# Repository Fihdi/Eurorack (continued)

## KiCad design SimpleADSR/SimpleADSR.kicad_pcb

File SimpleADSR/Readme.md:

# ADSR module with voltage controllable Sustain level and Release time.

I wasn't using the CV-Features of my VCADSR module at all so I cut out all of the unnecessary CV-parts. At the end I was still left with a pretty big schematic, so I started to reduce it. The finished module now has the following features:

Attack:		Sets the Attack time.

Decay:		Sets the Decay time.

Sustain:	Sets the Sustain level. This can be controlled externally with a control voltage on the SUS input.

Release:	Sets the Release time. This can be controlled externall with a control voltage on the CV input.

GATE:		Gate input, main input to use the module, goes into the decay and sustain phases while this input is high.

TRG:		Trigger input, the module starts the Attack phase regardless in which phase the module currently is.

EOC:		End-of-cycle output, this output becomes high at the end of the release phase.

OUT:		ADSR output.

LOOP:		Loop switch, re-triggers the module at the end of the release phase. Same effect as connecting EOC to GATE or TRG.

Hacks:

Slew Rate Limiter: While the module is in the sustain phase, an external signal can be applied to the SUS input. A slewed version of this signal is output at the OUT jack. The "DECAY" knob controls the slew rate.

The module that you see in the picture above is using circuit boards that were fabricated by [PCBWay](https://www.pcbway.com/). They have excellent build quality and I can recommend using their service to build your own projects! I used the "Black" option for the soldermask and the surface has very deep and glossy black finish, which looks amazing, they also have an option for a "Matte Black" finish which I will try next time. Thank you PCBWay for sponsoring this module. They have very fast response times, not even 20 minutes after uploading the Gerber files I received an E-Mail notifying me about an error in my design (turns out I didn't complete the outline of a board). Afterwards I could re-upload the files and it all worked out. Their chatroom is also readily available, all my questions regarding pricing, delivery and technical details were answered right away in the chat!

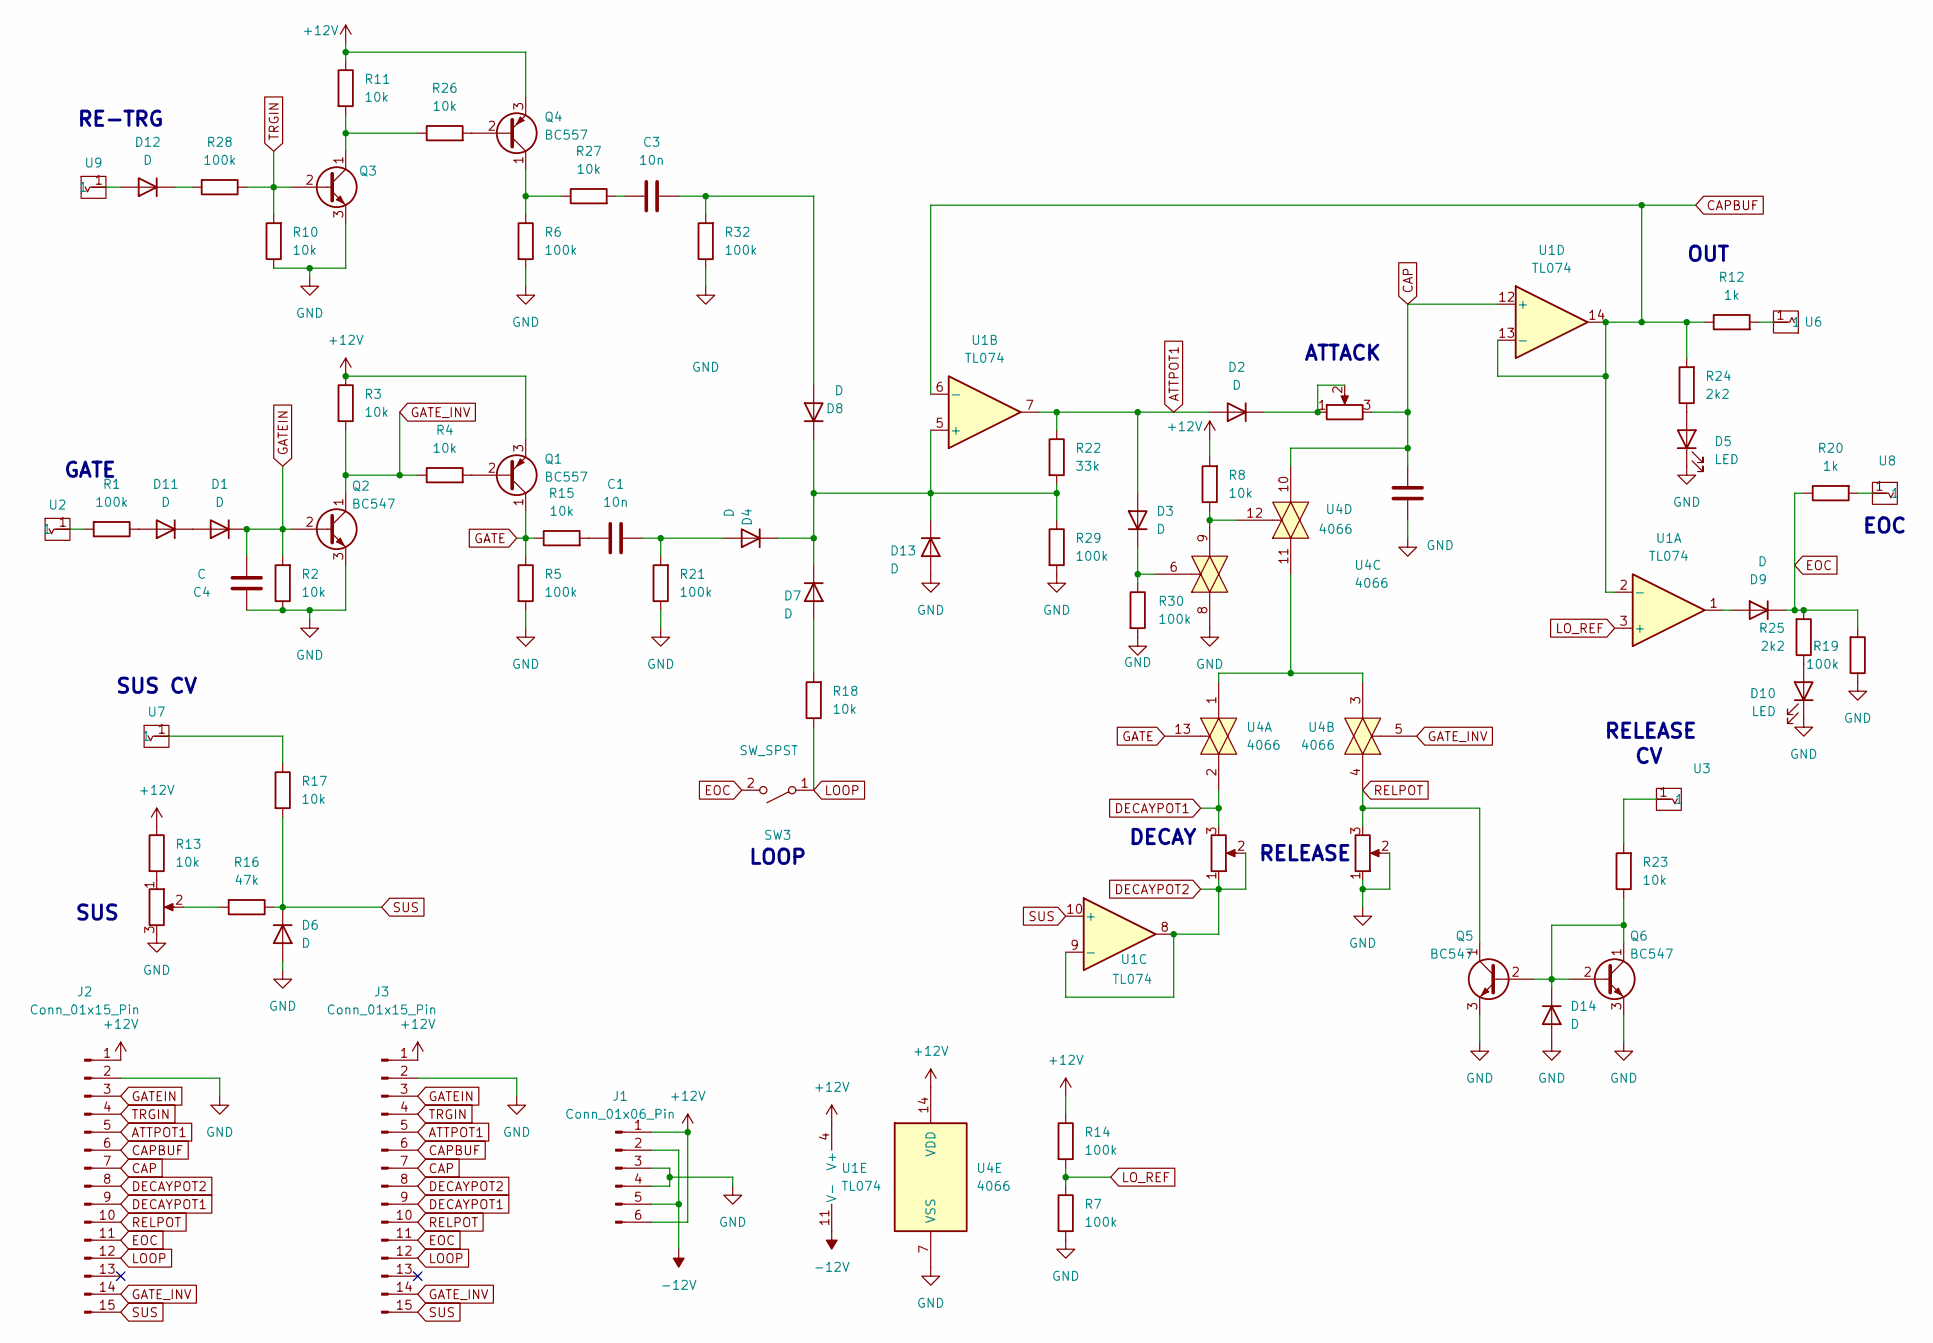
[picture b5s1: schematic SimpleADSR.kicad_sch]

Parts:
C1, C3: 10n; C_Axial_L5.1mm_D3.1mm_P10.00mm_Horizontal
C2, C4: C; C_Axial_L5.1mm_D3.1mm_P10.00mm_Horizontal
D1, D2, D3, D4, D6, D7, D8, D9, D11, D12, D13, D14: D; D_DO-34_SOD68_P7.62mm_Horizontal
D5, D10: LED; LED_D3.0mm
J1: Conn_01x06_Pin; PinHeader_1x06_P2.54mm_Vertical
J2, J3: Conn_01x15_Pin; PinSocket_1x15_P2.54mm_Vertical
Q1, Q4: BC557; TO-92L_Inline_Wide
Q2, Q3, Q5, Q6: BC547; TO-92L_Inline_Wide
R1, R5, R6, R7, R14, R19, R21, R28, R29, R30, R32: 100k; R_Axial_DIN0207_L6.3mm_D2.5mm_P7.62mm_Horizontal
R2, R3, R4, R8, R10, R11, R13, R15, R17, R18, R23, R26, R27: 10k; R_Axial_DIN0207_L6.3mm_D2.5mm_P7.62mm_Horizontal
R12, R20: 1k; R_Axial_DIN0207_L6.3mm_D2.5mm_P7.62mm_Horizontal
R16: 47k; R_Axial_DIN0207_L6.3mm_D2.5mm_P7.62mm_Horizontal
R22: 33k; R_Axial_DIN0207_L6.3mm_D2.5mm_P7.62mm_Horizontal
R24, R25: 2k2; R_Axial_DIN0207_L6.3mm_D2.5mm_P7.62mm_Horizontal
RV1, RV2, RV3, RV4: R_Potentiometer; AlpsPot
SW3: SW_SPST; PinHeader_1x02_P2.54mm_Vertical
U1: TL074; DIP-14_W7.62mm
U2, U3, U6, U7, U8, U9: Aux_flush; 3mm5 Mono Aux
U4: 4066; DIP-14_W7.62mm

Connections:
+12V: J1.1, J1.6, J2.1, J3.1, Q1.3 (E), Q4.3 (E), R3.1, R8.2, R11.1, R13.1, R14.1, U1.4 (V+), U4.14 (VDD)
-12V: J1.2, J1.5, U1.11 (V-)
ATTPOT1: D2.2 (A), D3.2 (A), J2.5, J3.5, R22.1, U1.7
CAP: C2.2, J2.7, J3.7, RV1.3, U1.12 (+), U4.10
CAPBUF: J2.6, J3.6, R12.1, R24.2, U1.2 (-), U1.6 (-), U1.13 (-), U1.14
DECAYPOT1: J2.9, J3.9, RV2.3, U4.2
DECAYPOT2: J2.8, J3.8, RV2.1, RV2.2, U1.8, U1.9 (-)
EOC: D9.1 (K), J2.11, J3.11, R19.2, R20.1, R25.2, SW3.2 (B)
GATE: Q1.1 (C), R5.1, R15.1, U4.13
GATEIN: C4.2, D1.1 (K), J2.3, J3.3, Q2.2 (B), R2.2
GATE_INV: J2.14, J3.14, Q2.1 (C), R3.2, R4.1, U4.5
GND: C2.1, C4.1, D5.1 (K), D6.2 (A), D10.1 (K), D13.2 (A), D14.2 (A), J1.3, J1.4, J2.2, J3.2, Q2.3 (E), Q3.3 (E), Q5.3 (E), Q6.3 (E), R2.1, R5.2, R6.2, R7.2, R10.1, R19.1, R21.1, R29.2, R30.2, R32.1, RV3.1, RV3.2, RV4.3, U4.7 (VSS), U4.8
LOOP: J2.12, J3.12, R18.1, SW3.1 (A)
LO_REF: R7.1, R14.2, U1.3 (+)
unnamed: C1.1, R15.2
unnamed: C3.1, R27.2
unnamed: D1.2 (A), D11.1 (K)
unnamed: D2.1 (K), RV1.1, RV1.2
unnamed: D3.1 (K), R30.1, U4.6
unnamed: C1.2, D4.2 (A), R21.2
unnamed: D5.2 (A), R24.1
unnamed: D7.2 (A), R18.2
unnamed: C3.2, D8.2 (A), R32.2
unnamed: D9.2 (A), U1.1
unnamed: D10.2 (A), R25.1
unnamed: D11.2 (A), R1.1
unnamed: D12.2 (A), U9.1
unnamed: D12.1 (K), R28.2
unnamed: D4.1 (K), D7.1 (K), D8.1 (K), D13.1 (K), R22.2, R29.1, U1.5 (+)
unnamed: D14.1 (K), Q5.2 (B), Q6.1 (C), Q6.2 (B), R23.1
unnamed: Q1.2 (B), R4.2
unnamed: Q3.1 (C), R11.2, R26.1
unnamed: Q4.2 (B), R26.2
unnamed: Q4.1 (C), R6.1, R27.1
unnamed: R1.2, U2.1
unnamed: R8.1, U4.9, U4.12
unnamed: R12.2, U6.1
unnamed: R13.2, RV4.1
unnamed: R16.2, RV4.2
unnamed: R17.1, U7.1
unnamed: R20.2, U8.1
unnamed: R23.2, U3.1
unnamed: U4.1, U4.3, U4.11
RELPOT: J2.10, J3.10, Q5.1 (C), RV3.3, U4.4
SUS: D6.1 (K), J2.15, J3.15, R16.1, R17.2, U1.10 (+)
TRGIN: J2.4, J3.4, Q3.2 (B), R10.2, R28.1

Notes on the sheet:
ATTACK
DECAY
LOOP
RELEASE
RE-TRG
SUS
GATE
SUS CV
EOC
OUT

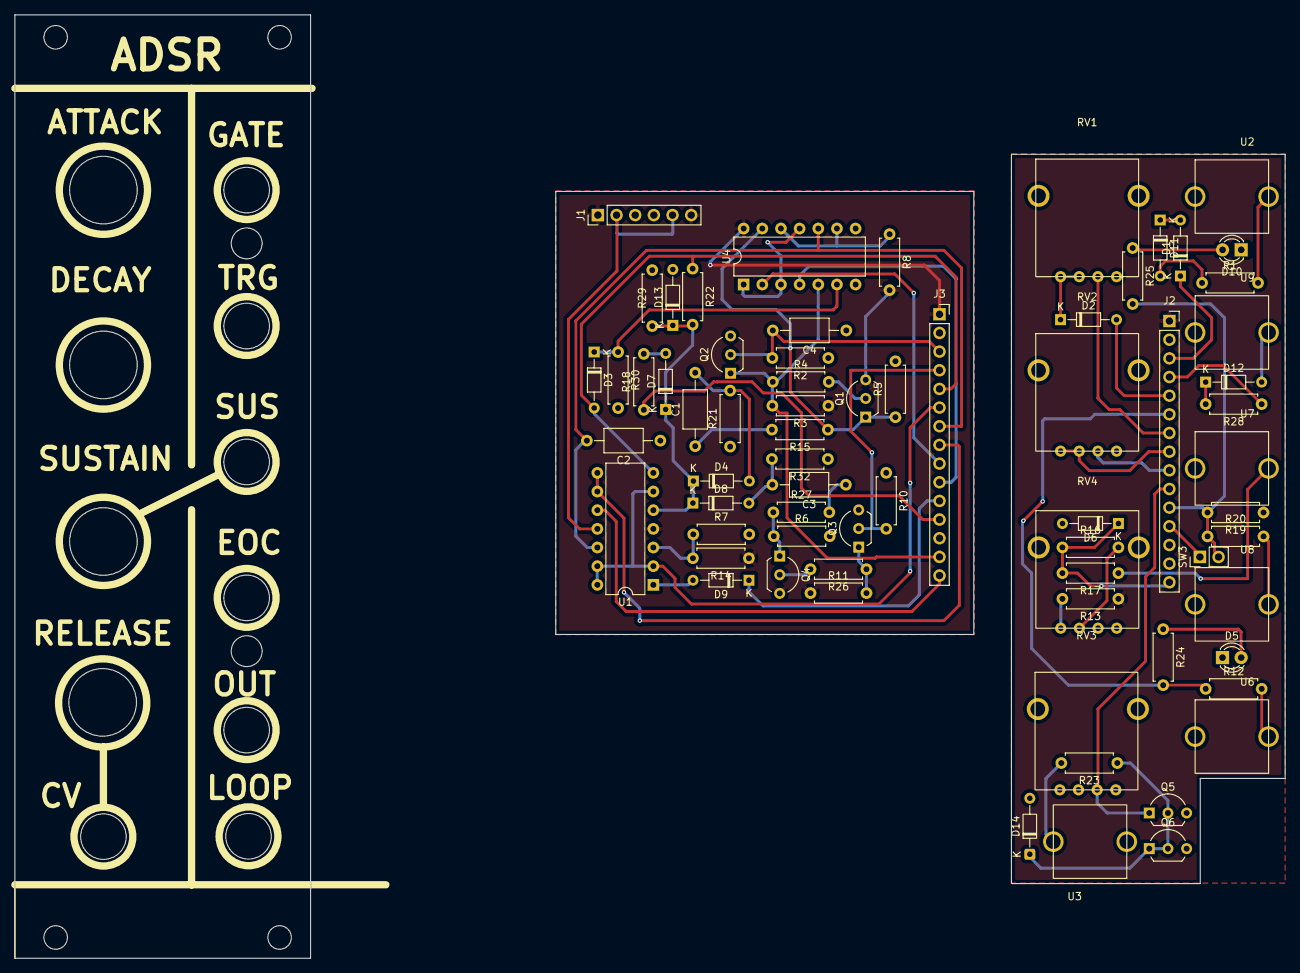
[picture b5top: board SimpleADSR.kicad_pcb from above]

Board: 2 copper layers, 172.9 x 128.4 mm, 70 parts (0 on the bottom side), 46 nets.

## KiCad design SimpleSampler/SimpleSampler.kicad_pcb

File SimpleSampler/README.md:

An improved Sampler module based on the Daisy Seed by Electrosmith.

The sample can be selected via a rotary encoder and the playback speed can be changed via a knob or an external CV. A Gate signal to the RANDOM input will select a random sample.

Depending on the PART/ENTIRE switch, the sample will either play in its entirity or only play while the gate signal is active.

A few notes on the circuit design choices:

Almost everyone uses MCP6002 OpAmps to sum and feed control voltages to microcrontrollers. The reasons for these are:

- Safety: The MCP6002 can only output up to 3.3V, which is the maximum voltage the pins can handle, so the OpAmp will never apply a higher voltage than what is safe.
- Easy summing: The summing of control voltages can be done with a single Opamp by adding a negative voltage of around -10V to the external voltage. Since its a summing amplifier with only one stage, the -10 volts will be flipped to a positive polarity on the other side, which is safe for the microcontroller and (again) it cannot go over the safe 3.3V.
- This summing approach does not work so well with a lot of JFET input Opamps (like the TL074) because of the "phase reversal" mode that can happen when the opamps pin is lower than around -8V.

The reason I still went with the TL074 is to safe an IC in the schematic. The safety aspect can be achieved with protection diodes and resistors as well, but the audio output of the Daisy Seed also needs to be amplified to regular Eurorack levels, which is not possible with the MCP6002, so a TL074 it is.

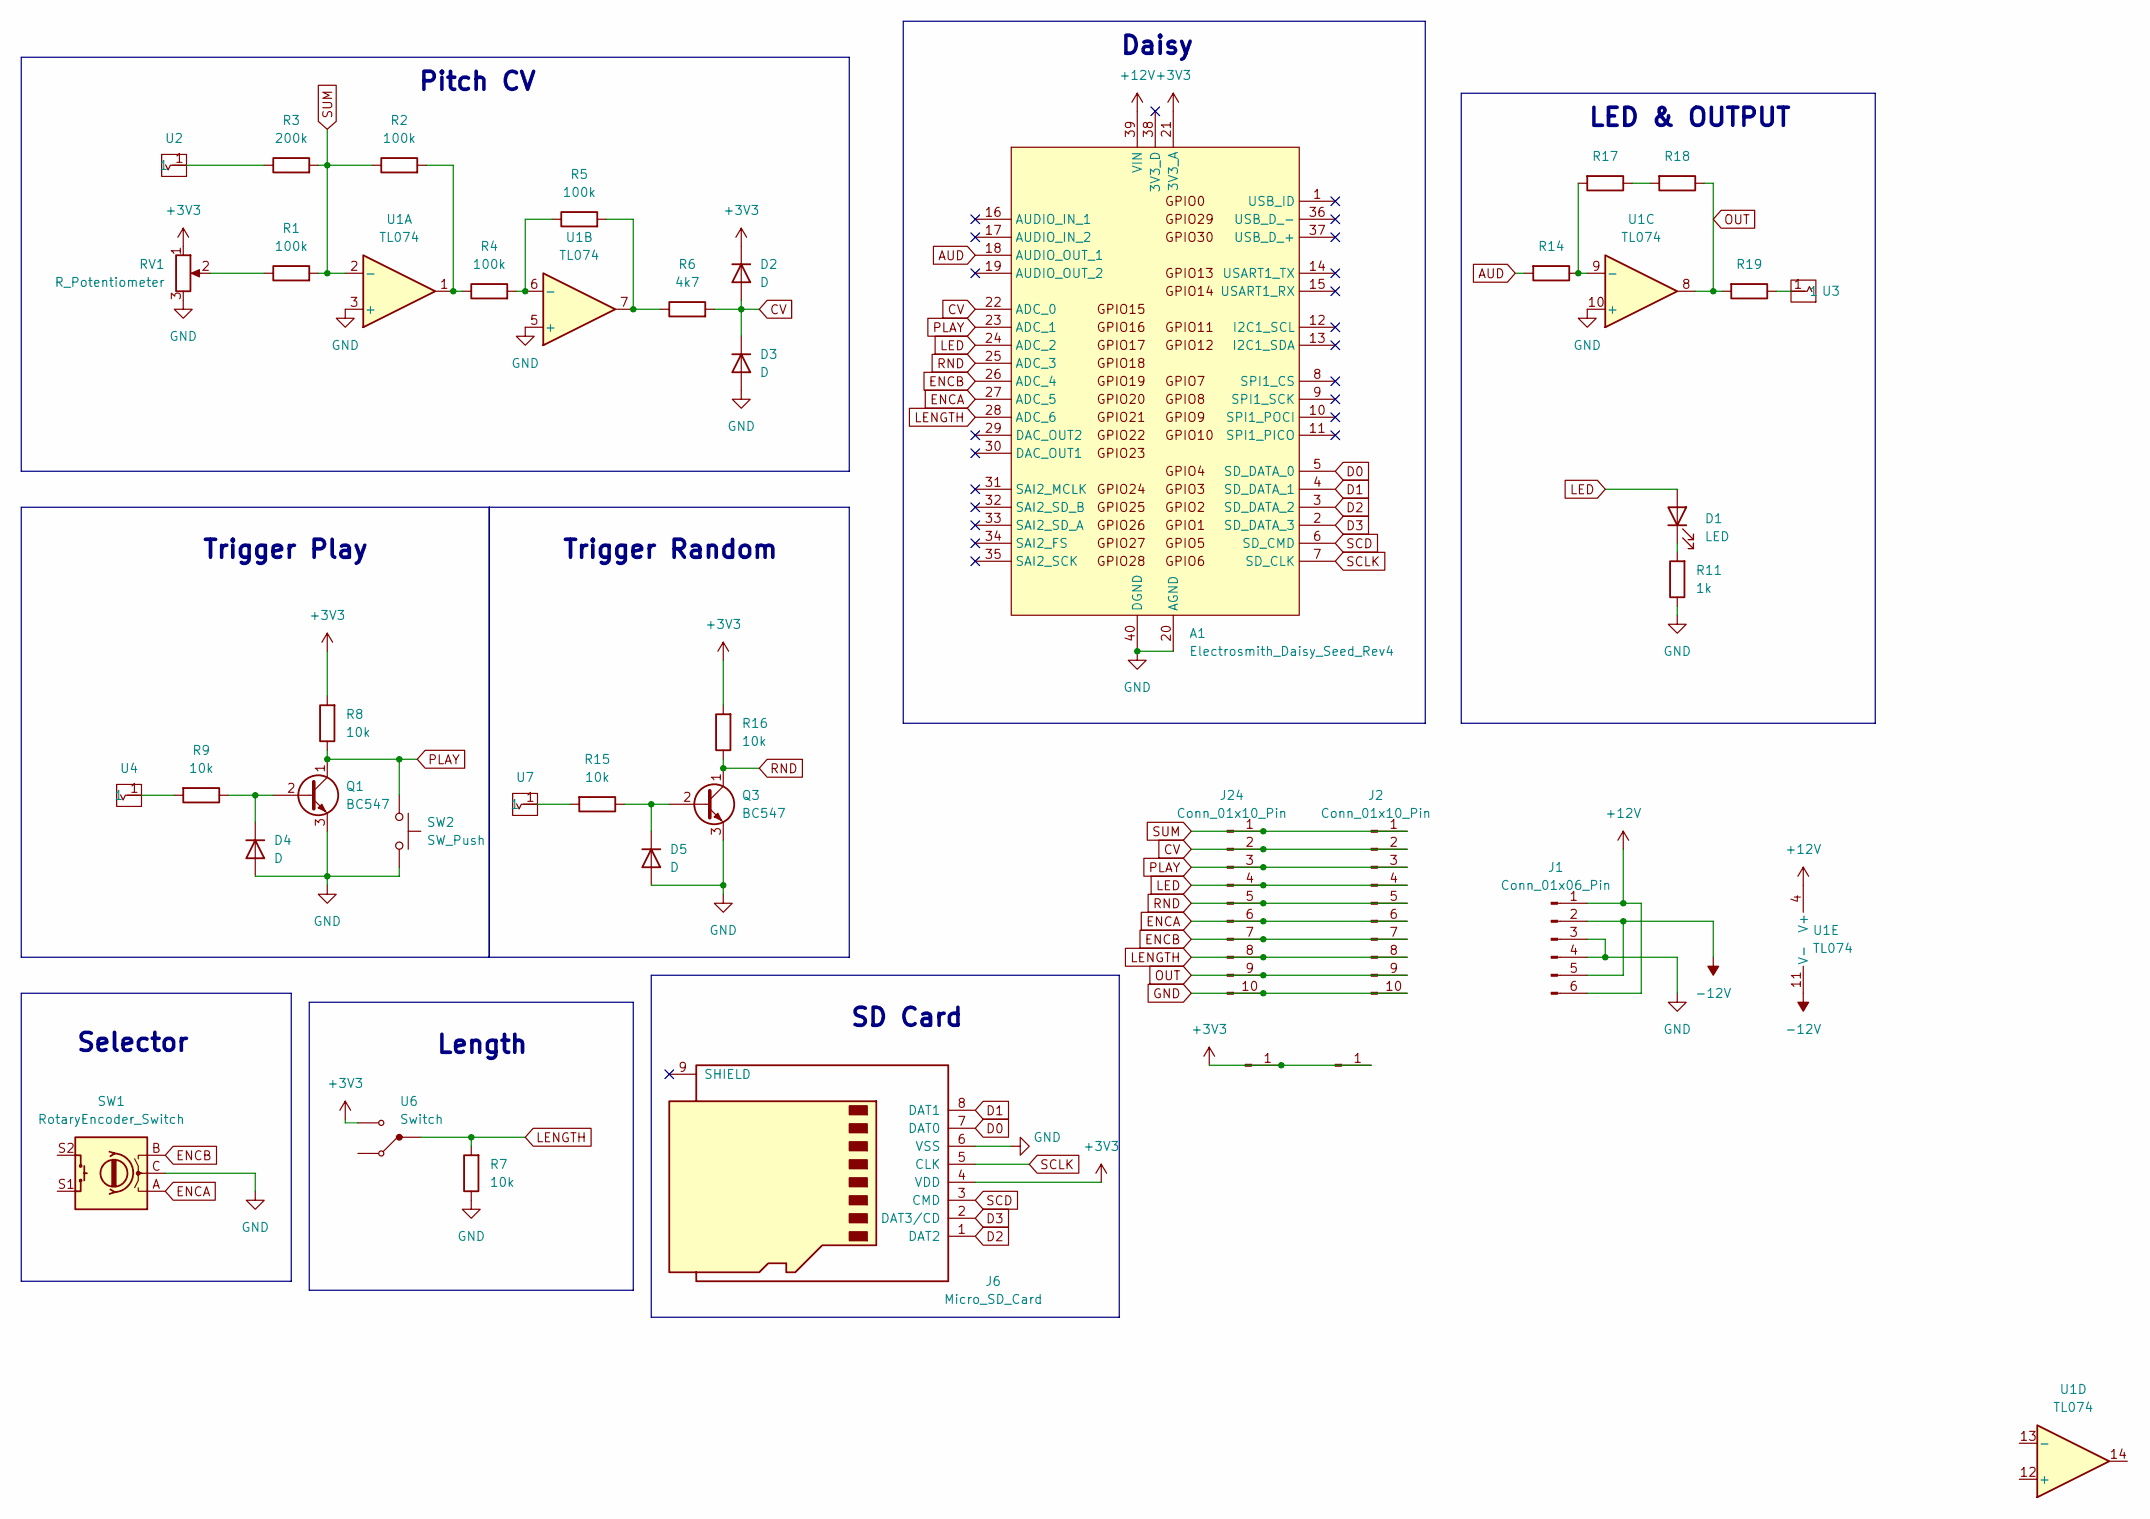
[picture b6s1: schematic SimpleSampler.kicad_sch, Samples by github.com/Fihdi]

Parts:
A1: Electrosmith_Daisy_Seed_Rev4; Electrosmith_Daisy_Seed
D1: LED; LED_D5.0mm
D2, D3, D4, D5: D; D_A-405_P7.62mm_Horizontal
J1: Conn_01x06_Pin; PinHeader_1x06_P2.54mm_Vertical
J2, J24: Conn_01x10_Pin; PinHeader_1x10_P2.54mm_Vertical
J3, J4: Conn_01x01_Pin; PinHeader_1x01_P2.54mm_Vertical
J6: Micro_SD_Card; microSD_HC_Molex_47219-2001
Q1, Q3: BC547; TO-92_Inline_Wide
R1, R2, R4, R5: 100k; R_Axial_DIN0207_L6.3mm_D2.5mm_P7.62mm_Horizontal
R3: 200k; R_Axial_DIN0207_L6.3mm_D2.5mm_P7.62mm_Horizontal
R6: 4k7; R_Axial_DIN0207_L6.3mm_D2.5mm_P7.62mm_Horizontal
R7, R8, R9, R15, R16: 10k; R_Axial_DIN0207_L6.3mm_D2.5mm_P7.62mm_Horizontal
R11: 1k; R_Axial_DIN0207_L6.3mm_D2.5mm_P7.62mm_Horizontal
R14, R17, R18, R19: R_Axial_DIN0207_L6.3mm_D2.5mm_P7.62mm_Horizontal
RV1: R_Potentiometer; AlpsPot
SW1: RotaryEncoder_Switch; RotaryEncoder_Alps_EC11E-Switch_Vertical_H20mm
SW2: SW_Push; PushButton
U1: TL074; DIP-14_W7.62mm
U2, U3, U4, U7: Aux_flush; 3mm5 Mono Aux
U6: Switch

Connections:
+3V3: A1.21 (3V3_A), D2.1 (K), J3.1, J4.1, J6.4 (VDD), R8.2, R16.2, RV1.1, U6.3
+12V: A1.39 (VIN), J1.1, J1.6, U1.4 (V+)
-12V: J1.2, J1.5, U1.11 (V-)
AUD: A1.18 (AUDIO_OUT_1), R14.2
CV: A1.22 (ADC_0), D2.2 (A), D3.1 (K), J2.2, J24.2, R6.2
D0: A1.5 (SD_DATA_0), J6.7 (DAT0)
D1: A1.4 (SD_DATA_1), J6.8 (DAT1)
D2: A1.3 (SD_DATA_2), J6.1 (DAT2)
D3: A1.2 (SD_DATA_3), J6.2 (DAT3/CD)
ENCA: A1.27 (ADC_5), J2.6, J24.6, SW1.A
ENCB: A1.26 (ADC_4), J2.7, J24.7, SW1.B
GND: A1.20 (AGND), A1.40 (DGND), D3.2 (A), D4.2 (A), D5.2 (A), J1.3, J1.4, J2.10, J6.6 (VSS), J24.10, Q1.3 (E), Q3.3 (E), R7.1, R11.1, RV1.3, SW1.C, SW2.2, U1.3 (+), U1.5 (+), U1.10 (+)
LED: A1.24 (ADC_2), D1.2 (A), J2.4, J24.4
LENGTH: A1.28 (ADC_6), J2.8, J24.8, R7.2, U6.2
unnamed: D1.1 (K), R11.2
unnamed: D4.1 (K), Q1.2 (B), R9.1
unnamed: D5.1 (K), Q3.2 (B), R15.1
unnamed: R1.1, RV1.2
unnamed: R2.2, R4.1, U1.1
unnamed: R3.1, U2.1
unnamed: R5.2, R6.1, U1.7
unnamed: R9.2, U4.1
unnamed: R15.2, U7.1
unnamed: R17.1, R18.2
unnamed: R19.1, U3.1
unnamed: R4.2, R5.1, U1.6 (-)
unnamed: R14.1, R17.2, U1.9 (-)
OUT: J2.9, J24.9, R18.1, R19.2, U1.8
PLAY: A1.23 (ADC_1), J2.3, J24.3, Q1.1 (C), R8.1, SW2.1
RND: A1.25 (ADC_3), J2.5, J24.5, Q3.1 (C), R16.1
SCD: A1.6 (SD_CMD), J6.3 (CMD)
SCLK: A1.7 (SD_CLK), J6.5 (CLK)
SUM: J2.1, J24.1, R1.2, R2.1, R3.2, U1.2 (-)

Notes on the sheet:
Selector
Trigger Random
Trigger Play
LED & OUTPUT
Daisy
Length
Pitch CV
SD Card

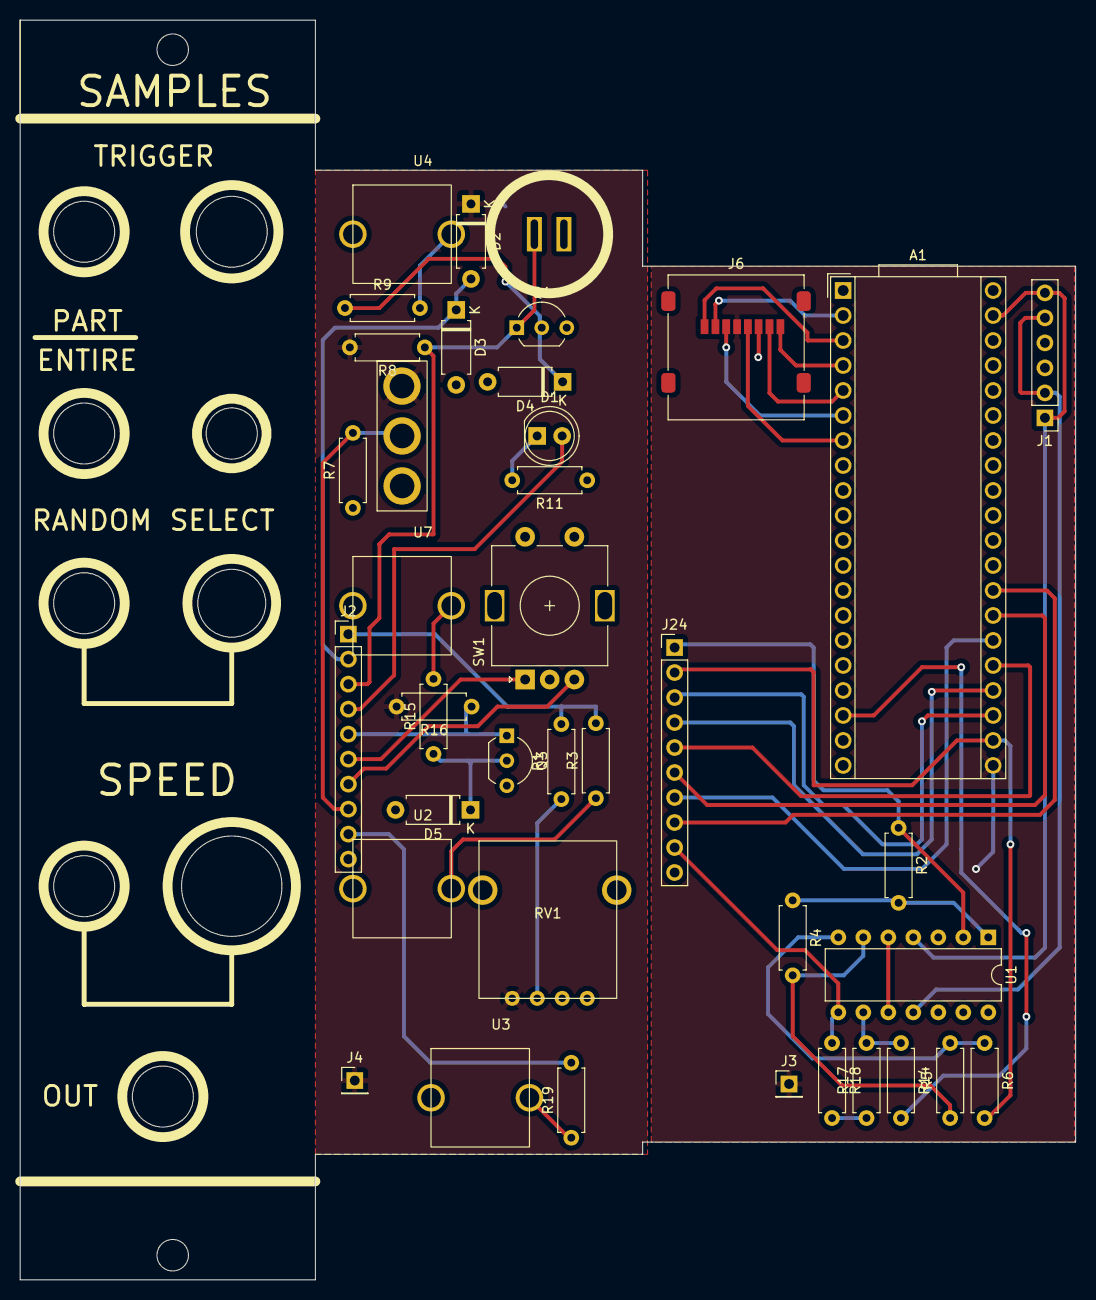
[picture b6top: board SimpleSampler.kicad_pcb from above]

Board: 2 copper layers, 107.2 x 128.0 mm, 39 parts (0 on the bottom side), 33 nets.

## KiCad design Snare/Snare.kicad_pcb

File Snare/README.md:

Snare module with CV control over the envelope accent, decay Time. The Decay Time can be controlled externally or with an internal random voltage generator.

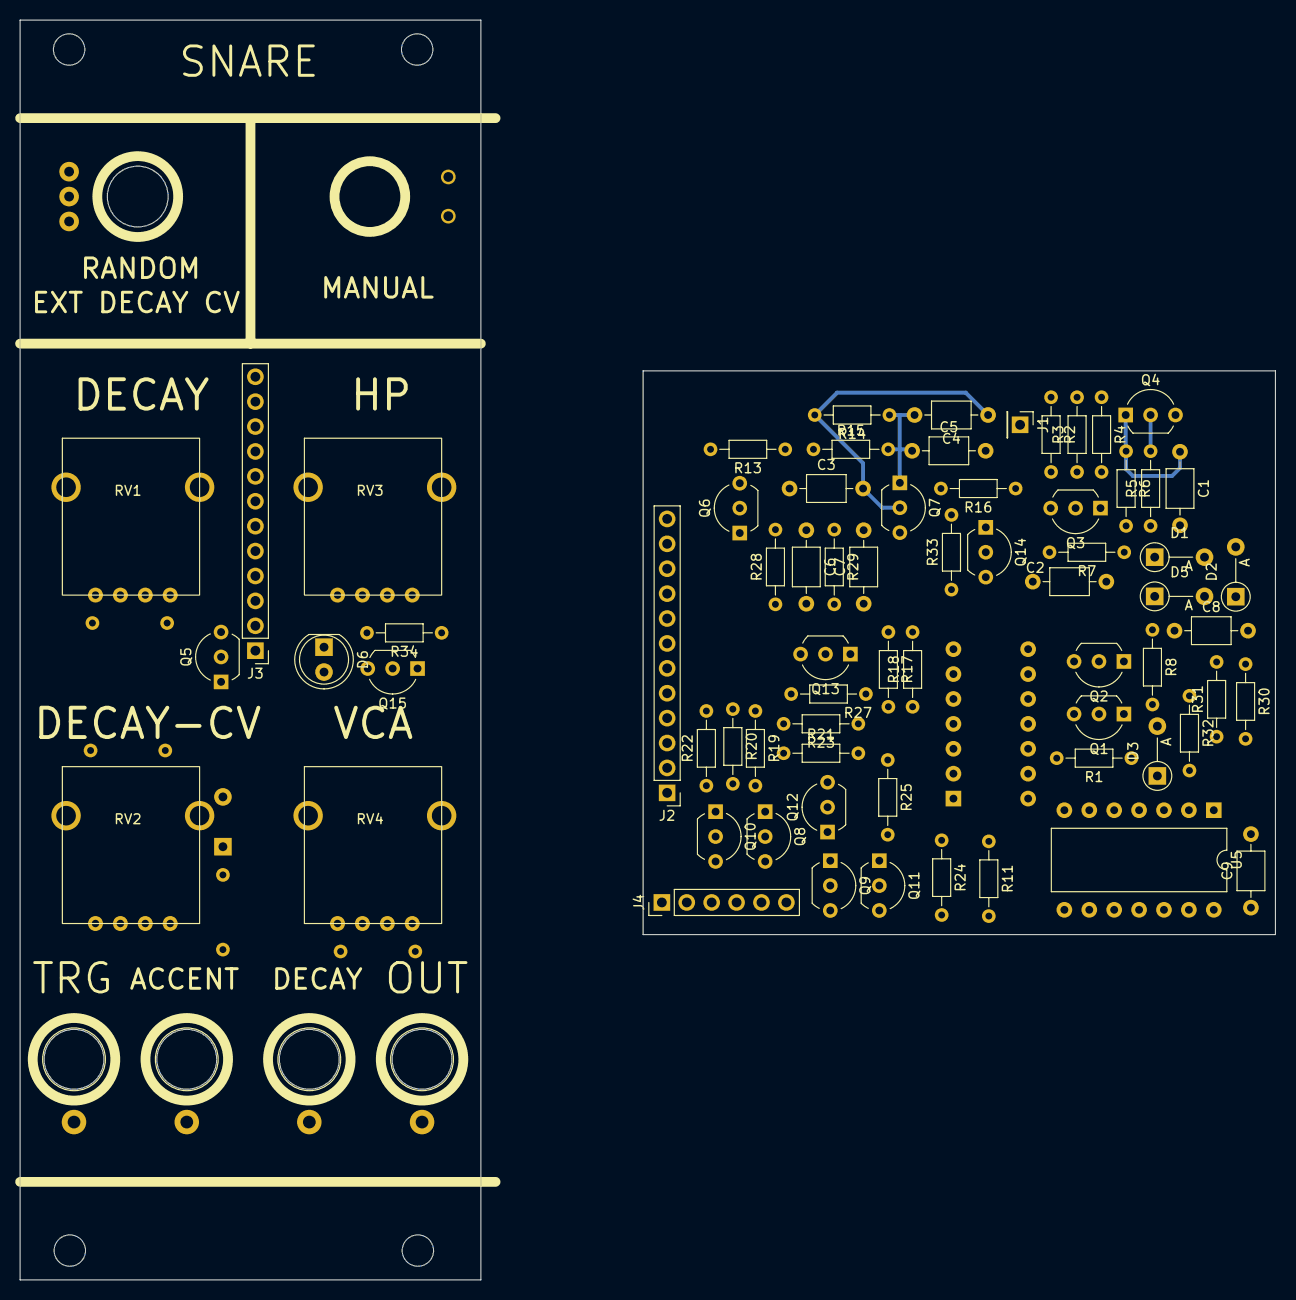
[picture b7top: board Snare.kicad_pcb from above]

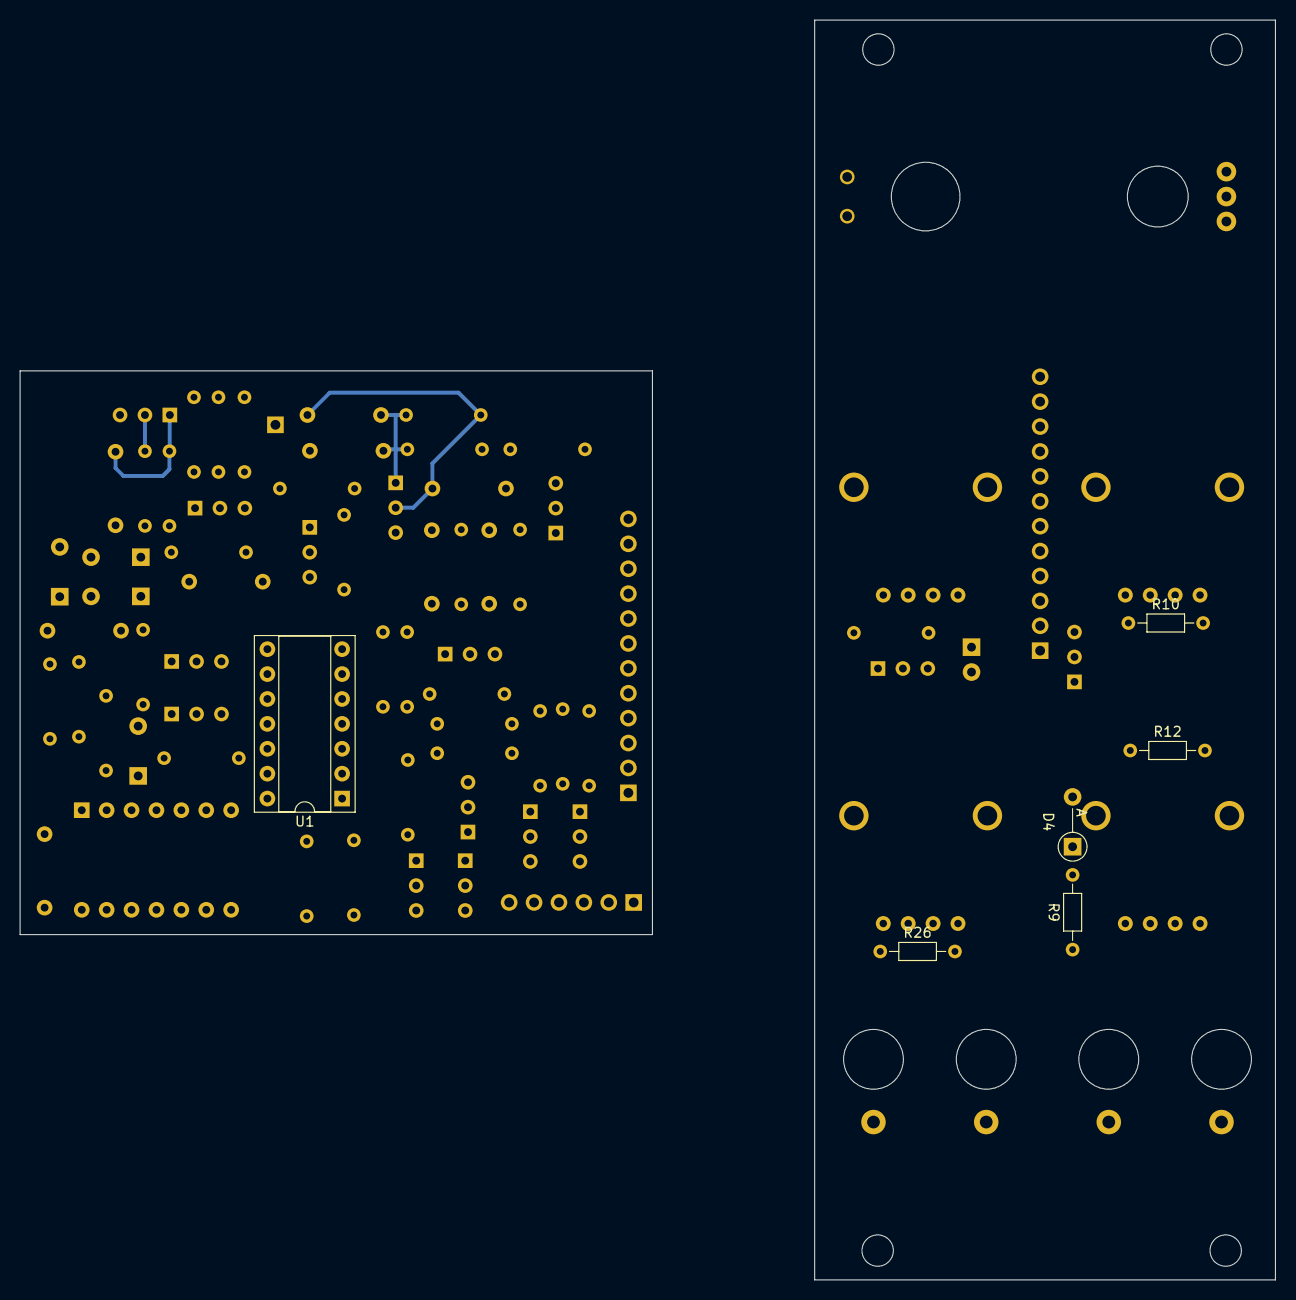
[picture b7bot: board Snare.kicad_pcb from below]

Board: 2 copper layers, 128.0 x 128.5 mm, 80 parts (6 on the bottom side), 50 nets.

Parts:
C1: 10n; C_Axial_L3.8mm_D2.6mm_P7.50mm_Horizontal
C2, C5, C6, C7: 470n; C_Axial_L3.8mm_D2.6mm_P7.50mm_Horizontal
C3: 100n; C_Axial_L3.8mm_D2.6mm_P7.50mm_Horizontal
C4: 10p; C_Axial_L3.8mm_D2.6mm_P7.50mm_Horizontal
C8, C9: C; C_Axial_L3.8mm_D2.6mm_P7.50mm_Horizontal
D1, D2, D3, D4, D5: D; D_A-405_P5.08mm_Vertical_AnodeUp
D6: LED; LED_D5.0mm
J1: Conn_01x01_Pin; PinHeader_1x01_P2.54mm_Vertical
J2, J3: Conn_01x12_Pin; PinHeader_1x12_P2.54mm_Vertical
J4: Conn_01x06_Pin; PinHeader_1x06_P2.54mm_Vertical
Q1, Q2, Q3, Q6, Q7, Q8, Q9, Q10, Q11, Q13, Q14, Q15: BC547; TO-92_Inline_Wide
Q4, Q5, Q12: BC557; TO-92_Inline_Wide
R1, R6, R7, R8, R10, R11, R12, R16, R17, R18, R19, R25, R26, R27, R28, R29, R30, R31, R33: 100k; R_Axial_DIN0204_L3.6mm_D1.6mm_P7.62mm_Horizontal
R2, R3, R4, R5: 10k; R_Axial_DIN0204_L3.6mm_D1.6mm_P7.62mm_Horizontal
R9, R13: 1M; R_Axial_DIN0204_L3.6mm_D1.6mm_P7.62mm_Horizontal
R14: 2M2; R_Axial_DIN0204_L3.6mm_D1.6mm_P7.62mm_Horizontal
R15: 4k7; R_Axial_DIN0204_L3.6mm_D1.6mm_P7.62mm_Horizontal
R20: 200R; R_Axial_DIN0204_L3.6mm_D1.6mm_P7.62mm_Horizontal
R21, R22: 50k; R_Axial_DIN0204_L3.6mm_D1.6mm_P7.62mm_Horizontal
R23, R24, R34: 200k; R_Axial_DIN0204_L3.6mm_D1.6mm_P7.62mm_Horizontal
R32: 1k; R_Axial_DIN0204_L3.6mm_D1.6mm_P7.62mm_Horizontal
RV1, RV2, RV3, RV4: R_Potentiometer; AlpsPot
SW1: SW_Push; Push_Flush
SW2: SW_SPDT; switch_flush
U1: TL074; DIP-14_W7.62mm_Socket
U2, U3, U4, U6: Aux_flush; aux_flush
U5: 4066; DIP-14_W10.16mm

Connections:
+12V: J2.1, J3.1, J4.1, J4.6, Q4.3 (E), Q13.1 (C), Q14.1 (C), Q15.1 (C), R4.1, R13.1, R15.1, R21.2, R22.2, RV4.1, SW1.2, U1.4 (V+), U5.14 (VDD)
-12V: J2.3, J3.3, J4.2, J4.5, Q9.3 (E), Q11.3 (E), R27.2, RV1.3, U1.11 (V-)
CAP: J2.11, J3.11
DCV: R1.2, R11.2, U1.14
ENV: Q14.3 (E), R25.2, R33.1
GND: C2.1, C9.1, D3.2 (A), D4.2 (A), J2.2, J3.2, J4.3, J4.4, Q1.3 (E), Q2.3 (E), Q3.3 (E), Q5.1 (C), Q6.2 (B), Q7.3 (E), Q10.2 (B), Q12.2 (B), R6.2, R7.2, R16.2, R18.2, R20.1, R23.1, R28.2, R29.2, R30.2, R31.2, R33.2, R34.1, RV1.1, RV2.3, RV4.3, U1.12 (+), U5.7 (VSS)
IN: J2.12, J3.12
NOISE: C7.1, J2.4, J3.4, R17.1, R32.1, RV3.3, U1.7
NOISE_HP: J2.6, J3.6, Q13.3 (E), R27.1, RV3.1
NOISE_TONED: J2.5, J3.5, R19.1, RV3.2
unnamed: C6.1, C7.2, R29.1
unnamed: C1.2, D1.2 (A), R7.1
unnamed: C2.2, D1.1 (K), D5.2 (A), Q1.1 (C), Q5.3 (E), Q14.2 (B)
unnamed: C8.2, D2.2 (A), R30.1
unnamed: D2.1 (K), R31.1, U5.13
unnamed: D3.1 (K), R32.2, U5.2
unnamed: D4.1 (K), Q5.2 (B), R9.2
unnamed: D5.1 (K), R8.1
unnamed: D6.2 (A), Q15.3 (E)
unnamed: D6.1 (K), R34.2
unnamed: J1.1, R2.1
unnamed: J2.7, J3.7
unnamed: Q1.2 (B), Q2.1 (C), Q2.2 (B), R1.1, R8.2
unnamed: Q3.2 (B), R2.2, R3.1
unnamed: Q3.1 (C), R4.2, R5.1
unnamed: Q4.2 (B), R5.2
unnamed: C1.1, Q4.1 (C), R6.1
unnamed: C3.1, Q6.3 (E), R13.2
unnamed: C3.2, C4.1, Q7.2 (B), R14.2
unnamed: C4.2, C5.1, Q7.1 (C), R14.1, R15.2
unnamed: Q8.2 (B), R19.2, R20.2
unnamed: Q8.1 (C), R21.1, R23.2, U1.10 (+)
unnamed: Q10.1 (C), R22.1, R24.1, U1.9 (-)
unnamed: Q8.3 (E), Q9.1 (C), Q10.3 (E)
unnamed: Q9.2 (B), Q11.1 (C), Q11.2 (B), Q12.1 (C)
unnamed: Q12.3 (E), R25.1, R26.2
unnamed: C6.2, Q13.2 (B), R28.1
unnamed: R3.2, U2.1
unnamed: R9.1, U3.1
unnamed: R10.1, RV1.2
unnamed: R12.1, RV2.2
unnamed: SW2.1 (A), U4.1
unnamed: RV2.1, SW2.2 (B)
unnamed: C9.2, U1.3 (+), U5.1
unnamed: C5.2, R16.1, U1.5 (+)
unnamed: R17.2, R18.1, U1.6 (-)
OFFSET: J2.9, J3.9, R26.1, RV4.2
OUT: J2.10, J3.10, Q15.2 (B), R24.2, U1.8, U6.1
RVG: SW2.3 (C), U1.1, U1.2 (-)
VGND: J2.8, J3.8, R10.2, R11.1, R12.2, U1.13 (-)

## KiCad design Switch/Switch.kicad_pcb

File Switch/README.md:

Two Voltage Controlled Switches with analog logic outputs based on https://www.schmitzbits.de/switch.html

BUY THE FRONT AND BACKBOARD SEPERATELY. The first version of the SWITCH module had some bugs and a needlesly complicated circuitry. The board in the Folder "Switch2" is compatible to the front and uses a DG412 IC. 

Can be used as switches, SPDT switch, comparator, inverters, MIN/MAX.

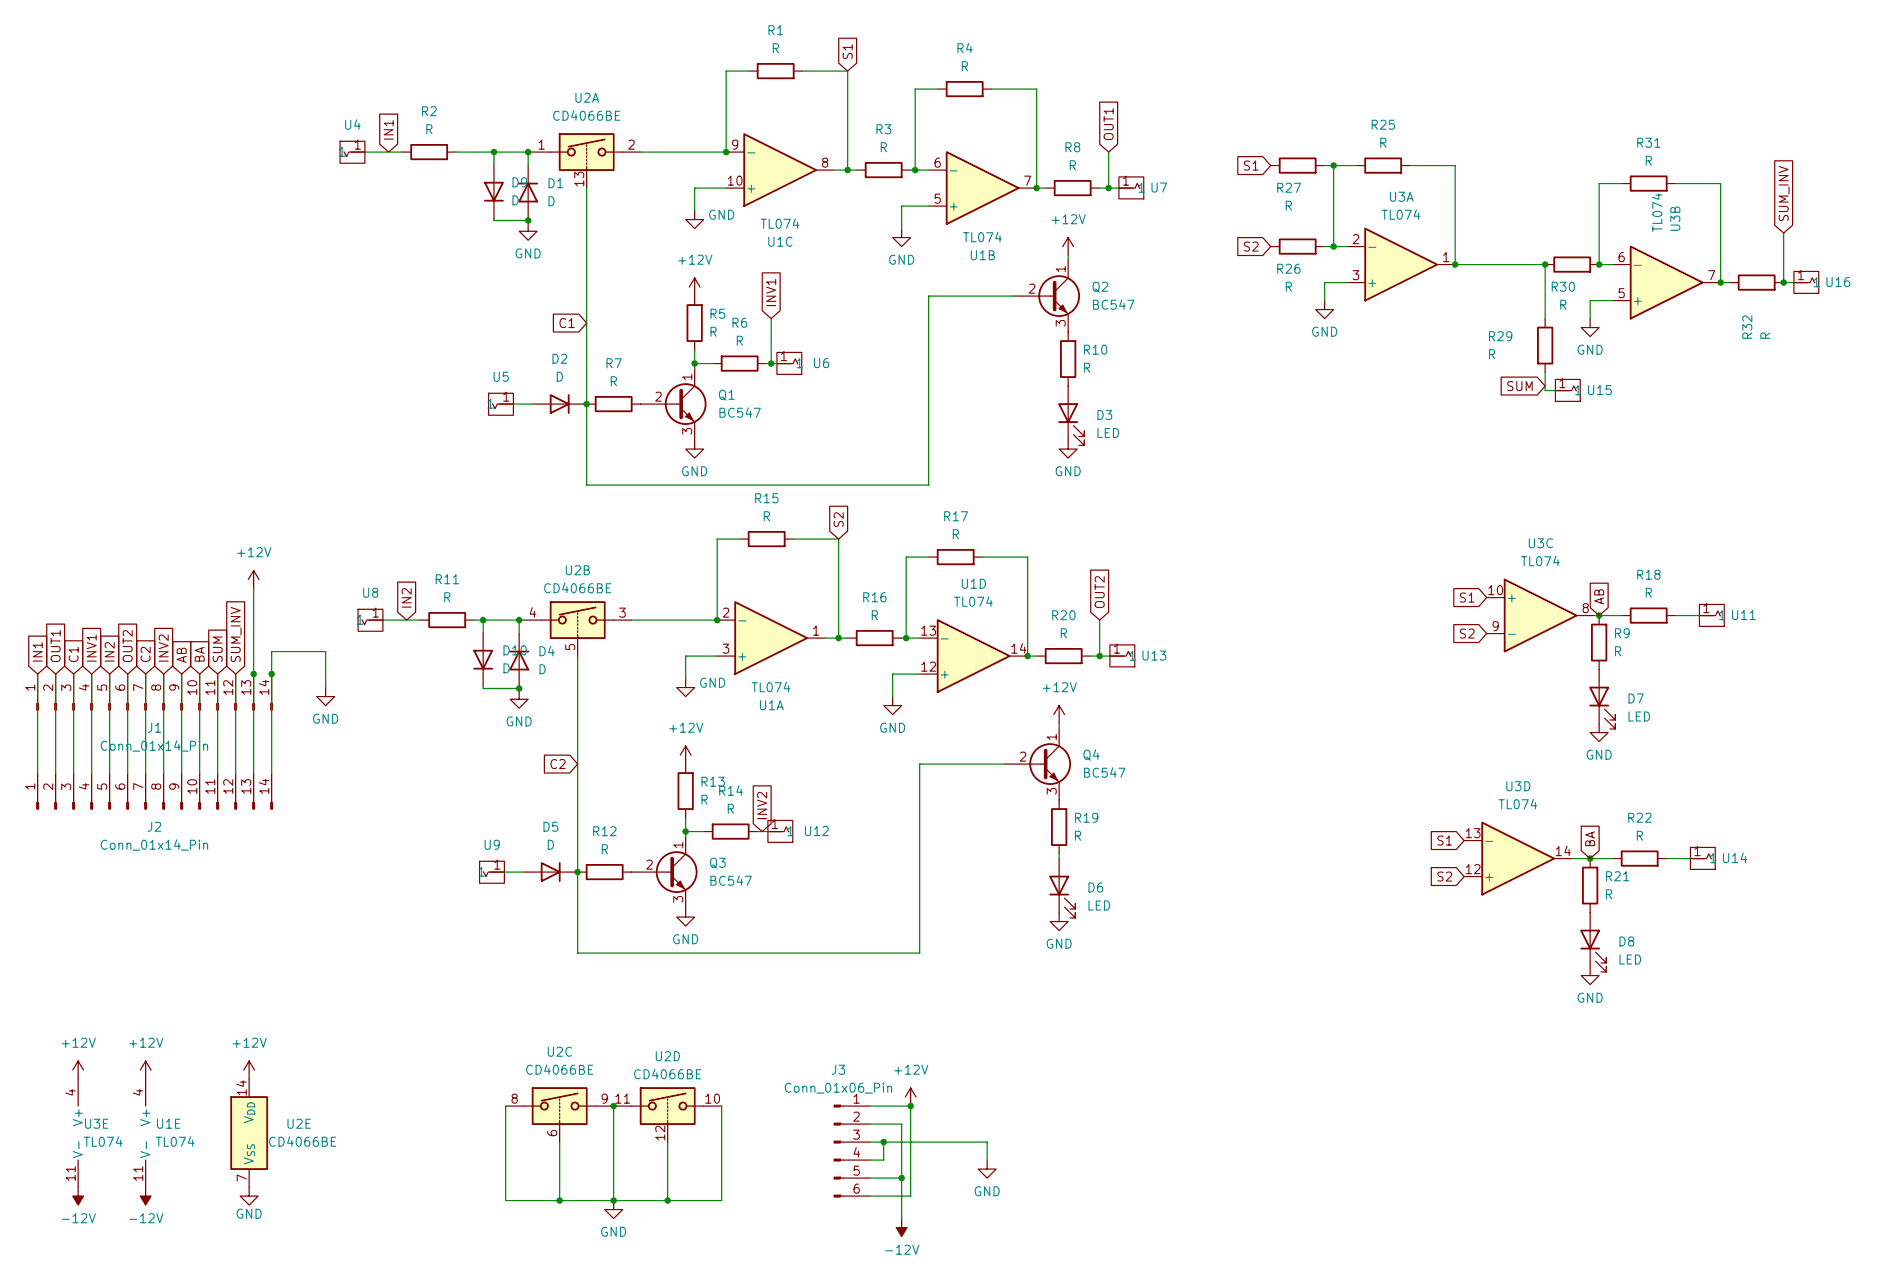
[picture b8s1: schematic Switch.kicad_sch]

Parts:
D1, D2, D4, D5, D9, D10: D; D_DO-34_SOD68_P5.08mm_Vertical_AnodeUp
D3, D6, D7, D8: LED; LED_D3.0mm
J1, J2: Conn_01x14_Pin; PinHeader_1x14_P2.54mm_Vertical
J3: Conn_01x06_Pin; PinHeader_1x06_P2.54mm_Vertical
Q1, Q2, Q3, Q4: BC547; TO-92L_Wide
R1, R2, R3, R4, R5, R6, R7, R8, R9, R10, R11, R12, R13, R14, R15, R16, R17, R18, R19, R20, R21, R22, R25, R26, R27, R29, R30, R31, R32: R; R_Axial_DIN0207_L6.3mm_D2.5mm_P7.62mm_Horizontal
U1, U3: TL074; DIP-14_W7.62mm_Socket
U2: CD4066BE; DIP-14_W7.62mm
U4, U5, U6, U7, U8, U9, U11, U12, U13, U14, U15, U16: Aux_flush; 3mm5 Mono Aux

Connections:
+12V: J1.13, J2.13, J3.1, J3.6, Q2.1 (C), Q4.1 (C), R5.2, R13.2, U1.4 (V+), U2.14 (V_{DD}), U3.4 (V+)
-12V: J3.2, J3.5, U1.11 (V-), U3.11 (V-)
AB: J1.9, J2.9, R9.2, R18.1, U3.8
BA: J1.10, J2.10, R21.2, R22.1, U3.14
C1: D2.1 (K), J1.3, J2.3, Q2.2 (B), R7.2, U2.13
C2: D5.1 (K), J1.7, J2.7, Q4.2 (B), R12.2, U2.5
GND: D1.2 (A), D3.1 (K), D4.2 (A), D6.1 (K), D7.1 (K), D8.1 (K), D9.1 (K), D10.1 (K), J1.14, J2.14, J3.3, J3.4, Q1.3 (E), Q3.3 (E), U1.3 (+), U1.5 (+), U1.10 (+), U1.12 (+), U2.6, U2.7 (V_{SS}), U2.8, U2.9, U2.10, U2.11, U2.12, U3.3 (+), U3.5 (+)
IN1: J1.1, J2.1, R2.1, U4.1
IN2: J1.5, J2.5, R11.1, U8.1
INV1: J1.4, J2.4, R6.1, U6.1
INV2: J1.8, J2.8, R14.1, U12.1
unnamed: D1.1 (K), D9.2 (A), R2.2, U2.1
unnamed: D2.2 (A), U5.1
unnamed: D3.2 (A), R10.1
unnamed: D5.2 (A), U9.1
unnamed: D6.2 (A), R19.1
unnamed: D7.2 (A), R9.1
unnamed: D8.2 (A), R21.1
unnamed: D4.1 (K), D10.2 (A), R11.2, U2.4
unnamed: Q1.2 (B), R7.1
unnamed: Q1.1 (C), R5.1, R6.2
unnamed: Q2.3 (E), R10.2
unnamed: Q3.2 (B), R12.1
unnamed: Q3.1 (C), R13.1, R14.2
unnamed: Q4.3 (E), R19.2
unnamed: R4.2, R8.1, U1.7
unnamed: R17.2, R20.1, U1.14
unnamed: R18.2, U11.1
unnamed: R22.2, U14.1
unnamed: R25.2, R29.1, R30.1, U3.1
unnamed: R31.2, R32.1, U3.7
unnamed: R15.1, U1.2 (-), U2.3
unnamed: R3.2, R4.1, U1.6 (-)
unnamed: R1.1, U1.9 (-), U2.2
unnamed: R16.2, R17.1, U1.13 (-)
unnamed: R25.1, R26.2, R27.2, U3.2 (-)
unnamed: R30.2, R31.1, U3.6 (-)
OUT1: J1.2, J2.2, R8.2, U7.1
OUT2: J1.6, J2.6, R20.2, U13.1
S1: R1.2, R3.1, R27.1, U1.8, U3.10 (+), U3.13 (-)
S2: R15.2, R16.1, R26.1, U1.1, U3.9 (-), U3.12 (+)
SUM: J1.11, J2.11, R29.2, U15.1
SUM_INV: J1.12, J2.12, R32.2, U16.1
